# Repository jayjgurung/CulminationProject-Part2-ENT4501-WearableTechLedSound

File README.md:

# Audio-Visual Reactive System Tech

By Jay Jung Gurung — Emerging Media Technology | Culmination Project II (MTEC 4501)

## Overview

Audio-Visual Reactive System Tech is an interactive hardware–software system that transforms real-time audio input into dynamic LED visualizations. Built using an ESP32 microcontroller, an I2S MEMS microphone, WS2812B LEDs, and a custom PCB, this project explores embedded systems, acoustics, digital signal processing, and wearable audiovisual design.

The system analyzes incoming sound using an FFT (Fast Fourier Transform) and maps frequency energy to visual patterns, brightness, and color behavior. Additional control inputs (potentiometers, infrared remote, buttons, sensors) allow the user to modify the visual output and sensitivity on the fly.

This project aims to create an elegant, portable, and customizable audio-reactive LED module suitable for performance, stage design, wearables, and experimental media-technology applications.

---

## Features

- Real-time audio analysis via ESP32 I2S interface
- FFT-driven LED visualization (frequency bins → light patterns)
- Custom PCB designed in KiCad 8/9
- 3D-printed enclosure modeled in Autodesk Fusion 360
- WS2812B LED output with multiple animation modes
- Potentiometer-based sensitivity control
- Optional IR remote support for future expansion
- Modular design for wearable or tabletop use

---

## Hardware Components

- ESP32-WROVER-IE DevKit
- INMP441 (or similar) I2S MEMS microphone
- WS2812B LED strip or 5-LED chain
- Potentiometer for sensitivity
- IR receiver (optional)
- USB-C Li-ion charging board
- 21700 lithium battery
- Custom PCB (routed & manufactured)
- 3D-printed casing

---

## Software / Tools

- Arduino IDE (ESP32 Core v3.x)
- KiCad 8/9 (schematic & PCB design)
- Autodesk Fusion 360 (enclosure modeling)
- FastLED library
- arduinoFFT library
- ESP-IDF I2S driver (new API)

---

## Repository Structure

```text
CULMINATIONPROJECT-PART2-ENT4501-WEARABLETECHLEDSOUND/
│
├── Agile_Reports/
│   ├── 01_Agile_Sprint_Entry.md
│   ├── 02_Agile_Sprint_Entry.md
│   ├── 03_Agile_Sprint_Entry.md
│   ├── 04_Agile_Sprint_Entry.md
│   ├── 05.1_Agile_Sprint_Entry.md
│   └── 05.2_Agile_Sprint_Entry.md
│
├── Docs/
│   ├── Budget Report/
│   ├── KiCad/
│   ├── Panel Feedback/
│   ├── Reference/
│   └── Timeline/
│
├── Iteration_Plans/
│   └── IterationPlan-Roadmap.md
│
├── Presentations/
│   ├── Culmination-Part1-ProgressReport_Presentation_Fall2024.pdf
│   ├── Jury#1 Presentation links -JayGurung-fall2025.md
│   ├── Presentation_#2_JayGurung.pptx
│   └── Presentation-w-video-link.md
│
├── src/
│   ├── Arduino IDE/
│   └── KiCad/
│
├── .gitignore
└── README.md
```

---

## System Workflow

1. Microphone captures audio through I2S
2. ESP32 samples audio (e.g., 16 kHz)
3. FFT processes frames (e.g., 1024 samples)
4. Frequency bins are mapped to LED color, brightness, and animations
5. Potentiometer adjusts sensitivity threshold
6. LEDs render animations in real time

---

## Visual Modes (examples)

- Low-frequency pulsing
- Mid-range bar-graph effect
- High-frequency sparkle
- Full-spectrum rainbow reactive
- Silence → idle animation

---

## Current Status

- Hardware wiring and soldering complete
- PCB v1 assembled and tested
- Audio capture and FFT working
- LED visualization stable
- Pot control implemented
- 3D casing in prototype stage

---

## Acknowledgements

- Mentored by Professor Dr. David Smith
- Open-source libraries: FastLED, arduinoFFT
- Espressif documentation & community forums

---

## License

This project is for academic use under MTEC 4501 at City Tech. Feel free to reference or fork with credit.
Audio-Visual Reactive System Tech

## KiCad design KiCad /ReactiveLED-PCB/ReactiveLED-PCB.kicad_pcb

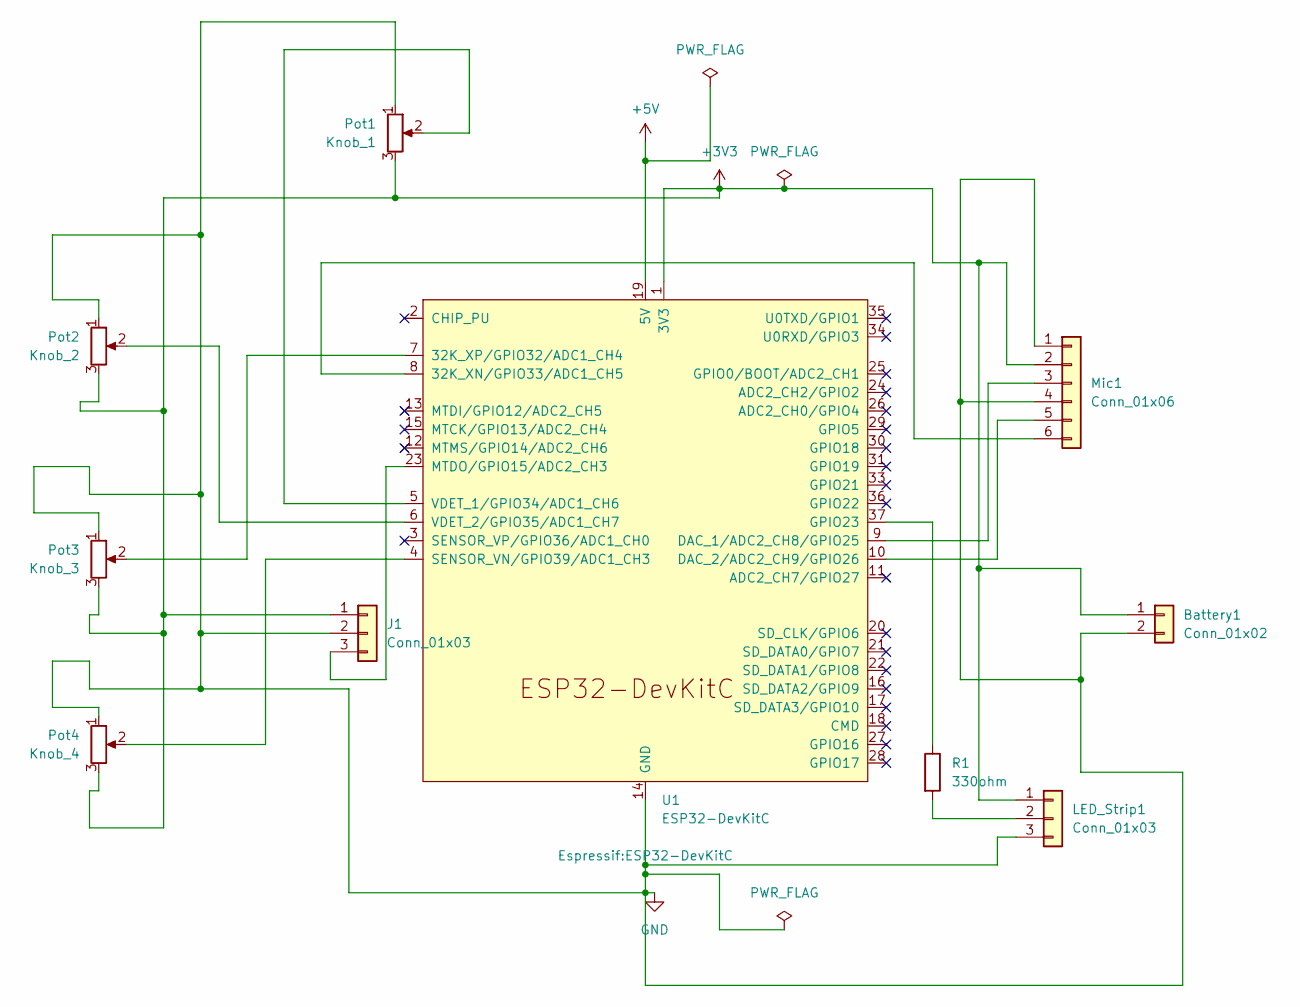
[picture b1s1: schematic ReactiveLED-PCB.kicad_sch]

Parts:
Battery1: Conn_01x02; JST_XH_B2B-XH-AM_1x02_P2.50mm_Vertical
J1: Conn_01x03; PinSocket_1x03_P2.54mm_Vertical
LED_Strip1: Conn_01x03; FanPinHeader_1x03_P2.54mm_Vertical
Mic1: Conn_01x06; PinHeader_1x06_P2.54mm_Vertical
Pot1: Knob_1; Potentiometer_Alps_RK163_Single_Horizontal
Pot2: Knob_2; Potentiometer_Alps_RK163_Single_Horizontal
Pot3: Knob_3; Potentiometer_Alps_RK163_Single_Horizontal
Pot4: Knob_4; Potentiometer_Alps_RK163_Single_Horizontal
R1: 330ohm; R_Axial_DIN0204_L3.6mm_D1.6mm_P7.62mm_Horizontal
U1: ESP32-DevKitC

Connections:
+3V3: Battery1.1, J1.1 (vcc), LED_Strip1.1, Mic1.2, Pot1.3, Pot2.3, Pot3.3, Pot4.3, U1.1 (3V3)
+5V: U1.19 (5V)
GND: Battery1.2, J1.2 (gnd), LED_Strip1.3, Mic1.1, Mic1.4, Pot1.1, Pot2.1, Pot3.1, Pot4.1, U1.14 (GND), U1.32 (GND), U1.38 (GND)
unnamed: J1.3 (out), U1.23 (MTDO/GPIO15/ADC2_CH3)
unnamed: LED_Strip1.2, R1.2
unnamed: Mic1.6, U1.8 (32K_XN/GPIO33/ADC1_CH5)
unnamed: Mic1.5, U1.10 (DAC_2/ADC2_CH9/GPIO26)
unnamed: Mic1.3, U1.9 (DAC_1/ADC2_CH8/GPIO25)
unnamed: Pot3.2, U1.7 (32K_XP/GPIO32/ADC1_CH4)
unnamed: R1.1, U1.37 (GPIO23)
unnamed: Pot4.2, U1.4 (SENSOR_VN/GPIO39/ADC1_CH3)
unnamed: Pot1.2, U1.5 (VDET_1/GPIO34/ADC1_CH6)
unnamed: Pot2.2, U1.6 (VDET_2/GPIO35/ADC1_CH7)

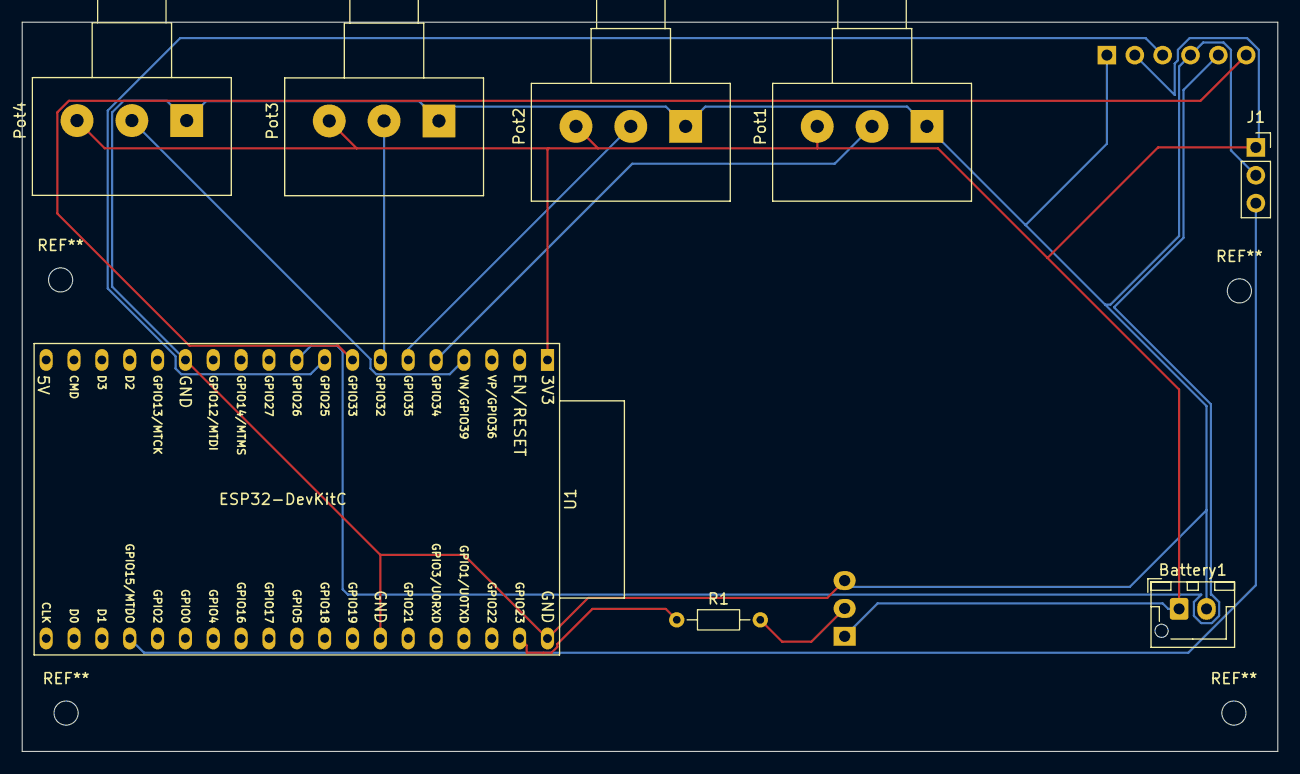
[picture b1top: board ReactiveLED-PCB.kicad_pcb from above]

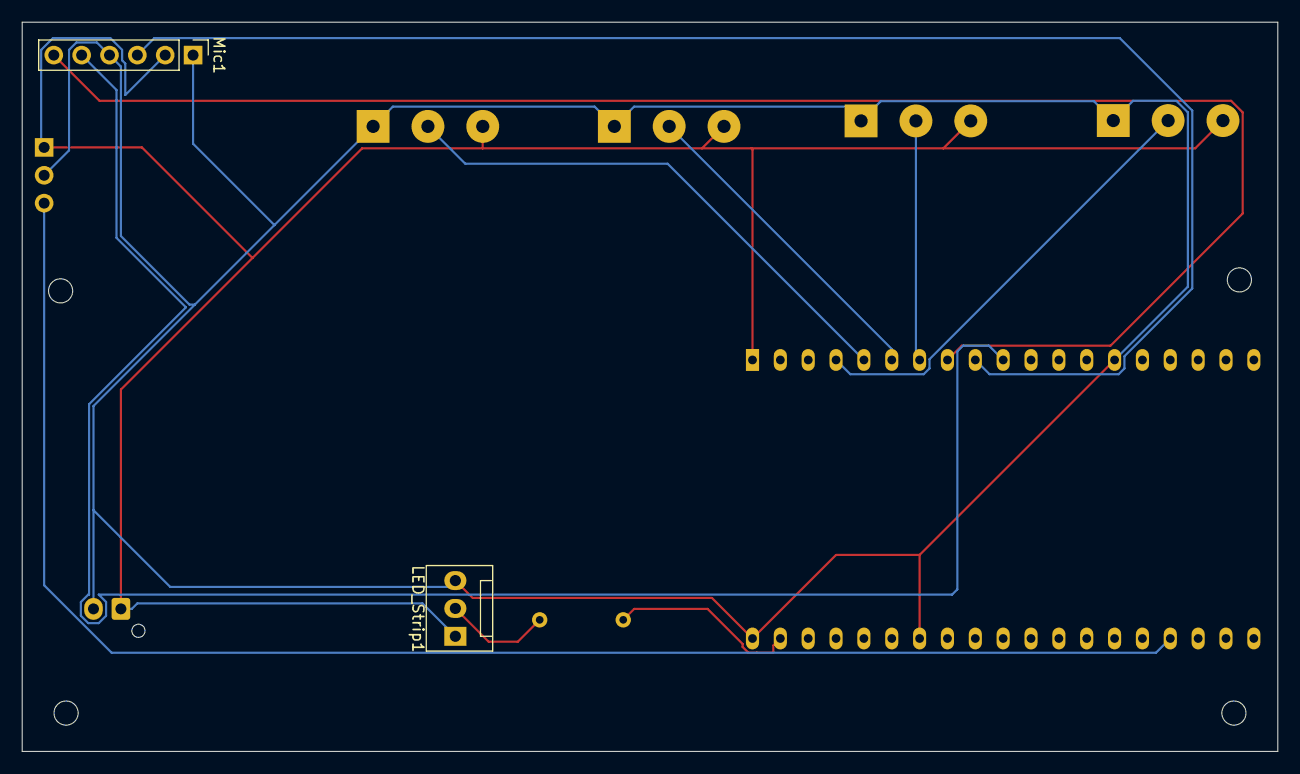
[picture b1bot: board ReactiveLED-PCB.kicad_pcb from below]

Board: 2 copper layers, 114.5 x 66.5 mm, 10 parts (2 on the bottom side), 12 nets.

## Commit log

2025-09-02 Repo First Update
    Repo and Folders created. Assets and documents added, Agile Report, Roadmap Created.
2025-09-02 Agile Report 2 Uploaded
    Research on the microphone modules and components.
2025-09-08 03_Agile_Sprint_Entry
    Added adult spin report number three.
2025-09-09 Update to Agile Report 3
    Minor updates
2025-09-30 Added Agile Report and Code update
2025-09-30 Report Updated
    Updated reports, slight corrections
2025-09-30 updated iteration road map
    Added more details about the roadmap
2025-09-30 added presentation
    added presentation to the repo
2025-09-30 Updated Presentation Link
2025-09-30 changed file names
2025-09-30 update
    some slight updates
2025-09-30 update
    update links
2025-10-26 Added iteration 5
    updated
2025-11-04 Added KiCad Files, New Sketch v.3
    Update
2025-11-25 Delete .DS_Store
    deleted
2025-11-25 Delete .vscode directory
    deleted junk file
2025-11-25 Updated
    sorted repository
2025-11-25 Updated
    quick update
2025-11-25 Rename Agile_Sprint_Entry.md to 05.1_Agile_Sprint_Entry.md
2025-11-25 update with dsstore
    added src folder
2025-11-25 moved around stuff
    updated dirs
2025-11-25 more updated
    clean up
2025-11-25 updated folder
    rearrangement
2025-11-25 Remove tracked .DS_Store files and add to .gitignore
2025-12-08 Updated Code Version 4
    Restored some PCb files that got accidentally deleted among another more files.
